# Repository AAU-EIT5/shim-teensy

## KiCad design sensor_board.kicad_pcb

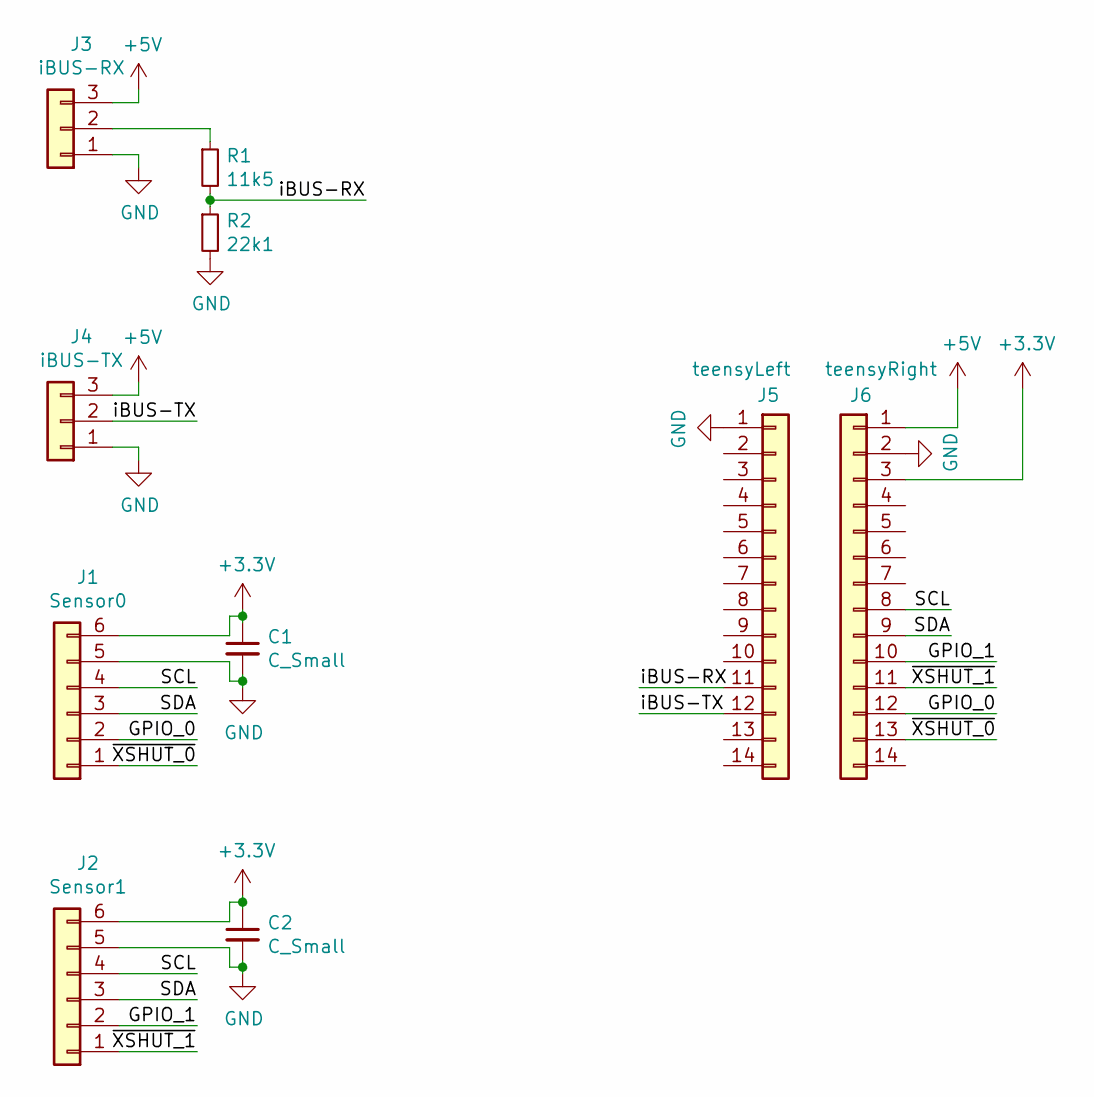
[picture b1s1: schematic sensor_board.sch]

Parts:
C1, C2: C_Small; C_0603_1608Metric_Pad1.05x0.95mm_HandSolder
J1: Sensor0; PinSocket_1x06_P2.54mm_Vertical
J2: Sensor1; PinSocket_1x06_P2.54mm_Vertical
J3: iBUS-RX; PinHeader_1x03_P2.54mm_Horizontal
J4: iBUS-TX; PinHeader_1x03_P2.54mm_Horizontal
J5: teensyLeft; PinSocket_1x14_P2.54mm_Vertical
J6: teensyRight; PinSocket_1x14_P2.54mm_Vertical
R1: 11k5; R_0603_1608Metric_Pad1.05x0.95mm_HandSolder
R2: 22k1; R_0603_1608Metric_Pad1.05x0.95mm_HandSolder

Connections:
+3V3: C1.1, C2.1, J1.6, J2.6, J6.3
+5V: J3.3, J4.3, J6.1
/GPIO_0: J1.2, J6.12
/GPIO_1: J2.2, J6.10
/SCL: J1.4, J2.4, J6.8
/SDA: J1.3, J2.3, J6.9
/iBUS-RX: J5.11, R1.2, R2.1
/iBUS-TX: J4.2, J5.12
/~XSHUT_0: J1.1, J6.13
/~XSHUT_1: J2.1, J6.11
GND: C1.2, C2.2, J1.5, J2.5, J3.1, J4.1, J5.1, J6.2, R2.2
unnamed: J3.2, R1.1

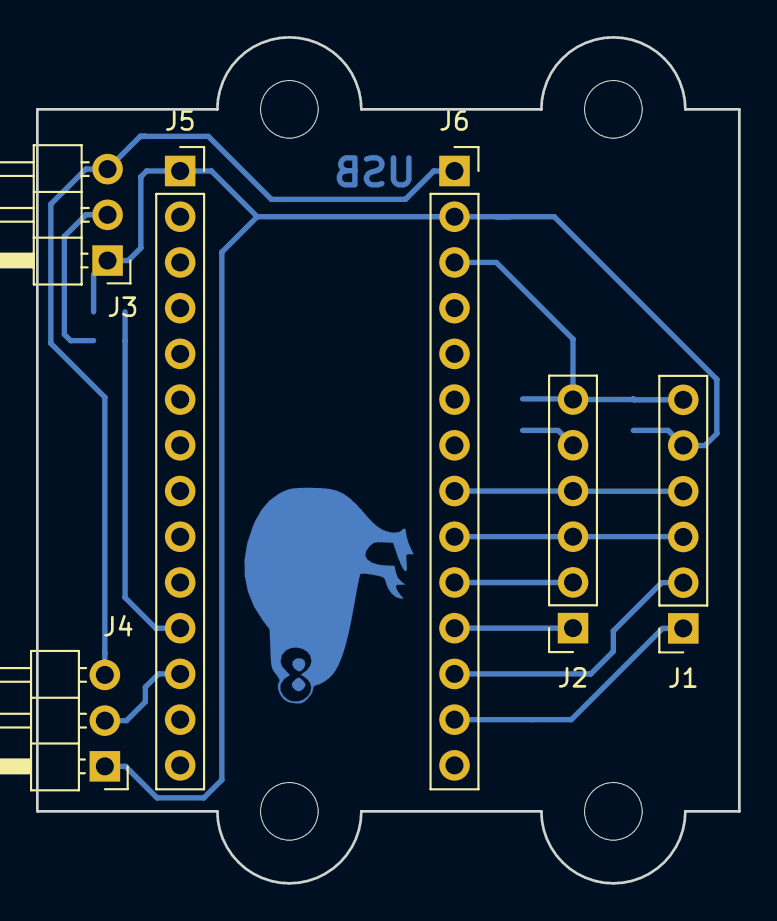
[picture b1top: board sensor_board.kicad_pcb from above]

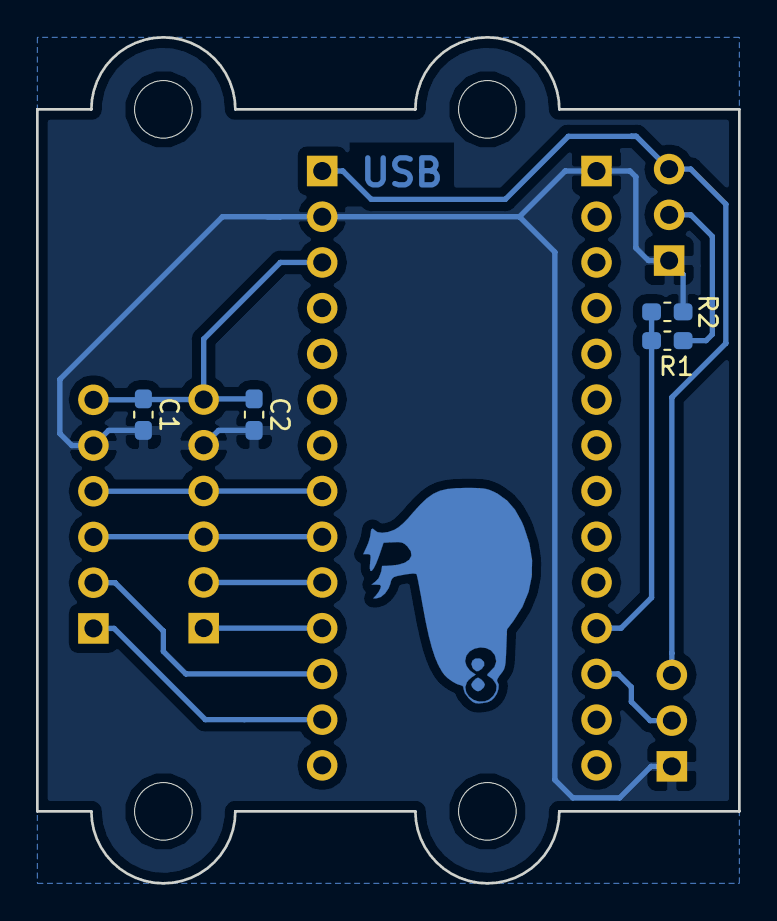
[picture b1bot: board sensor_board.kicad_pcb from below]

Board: 2 copper layers, 39.0 x 47.0 mm, 10 parts (4 on the bottom side), 12 nets.

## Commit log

2018-11-26 inital commit
2018-11-26 made it teensy
